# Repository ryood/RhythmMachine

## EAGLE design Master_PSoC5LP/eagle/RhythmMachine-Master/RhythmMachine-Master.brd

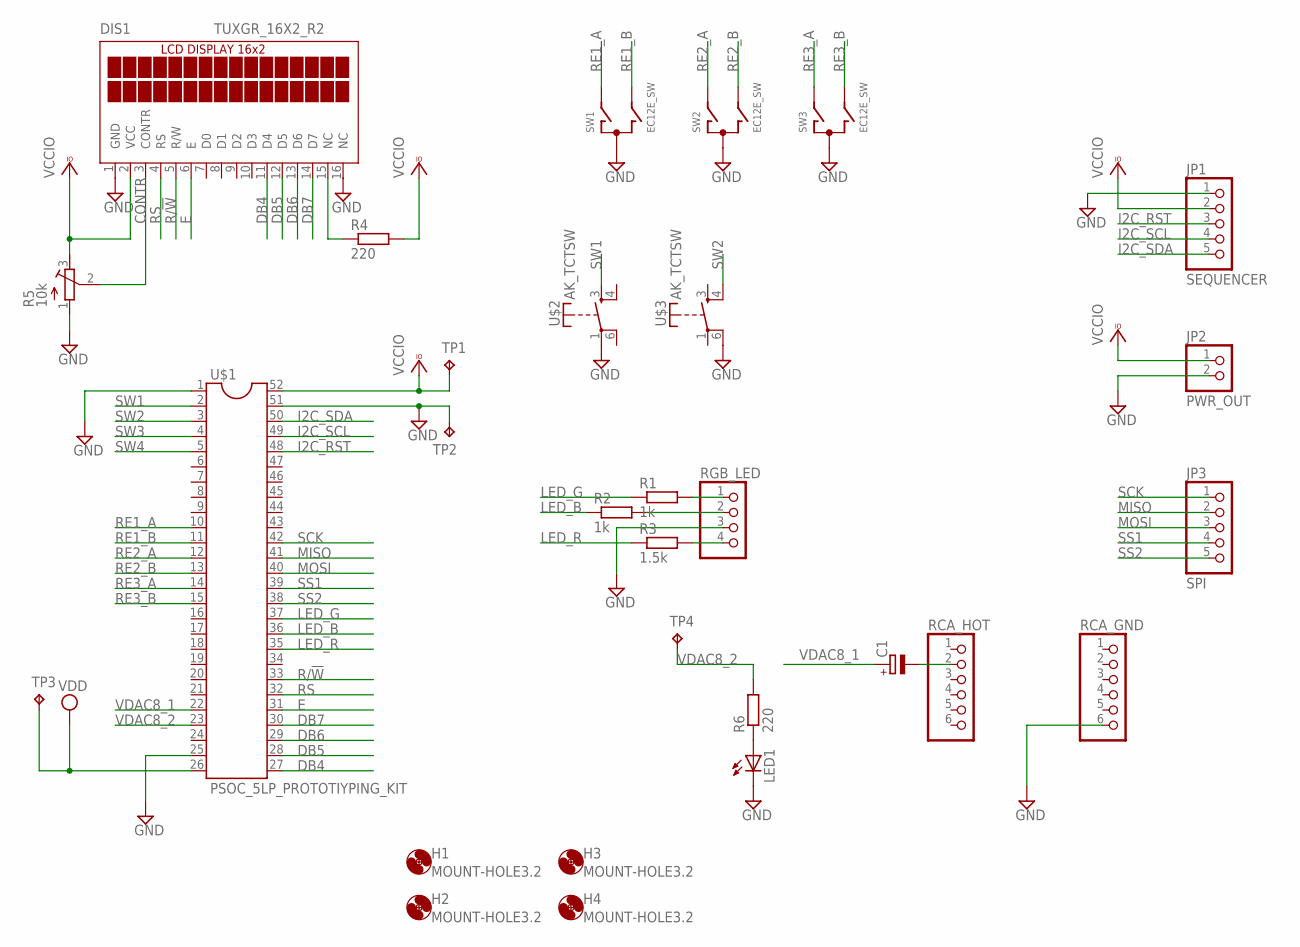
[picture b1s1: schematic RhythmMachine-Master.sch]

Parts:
C1: CPOL-EUE2.5-7; E2,5-7
DIS1: TUXGR_16X2_R2
H1, H2, H3, H4: MOUNT-HOLE3.2; 3,2
JP1: SEQUENCER; 1X05/90
JP2: PWR_OUT; 1X02/90
JP3: SPI; 1X05/90
LED1: LED3MM
R1, R2: 1k; 0207/7
R3: 1.5k; 0207/7
R4, R6: 220; 0207/7
R5: 10k; RTRIM3339P
RCA_GND: PINHD-1X6; 1X06
RCA_HOT: PINHD-1X6; 1X06
RGB_LED: PINHD-1X4; 1X04
SW1, SW2, SW3: EC12E_SW; ALPS_EC12E_SW
TP1, TP2, TP3, TP4: TPPAD1-13; P1-13
U$1: PSOC_5LP_PROTOTIYPING_KIT; DIL52-8
U$2, U$3: AK_TCTSW; TME1

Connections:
CONTR: DIS1.3 (CONTR), R5.2 (S)
DB4: DIS1.11 (D4), U$1.27
DB5: DIS1.12 (D5), U$1.28
DB6: DIS1.13 (D6), U$1.29
DB7: DIS1.14 (D7), U$1.30
E: DIS1.6 (E), U$1.31
GND: DIS1.1 (GND), DIS1.16 (NC), JP1.1, JP2.2, LED1.K (C), R5.1 (A), RCA_GND.6, RGB_LED.3, SW1.C, SW2.C, SW3.C, TP2.TP, U$1.1, U$1.25, U$1.51, U$2.1, U$3.6
I2C_RST: JP1.3, U$1.48
I2C_SCL: JP1.4, U$1.49
I2C_SDA: JP1.5, U$1.50
LED_B: R2.1, U$1.36
LED_G: R1.1, U$1.37
LED_R: R3.1, U$1.35
MISO: JP3.2, U$1.41
MOSI: JP3.3, U$1.40
unnamed: R1.2, RGB_LED.1
unnamed: R2.2, RGB_LED.2
unnamed: R3.2, RGB_LED.4
unnamed: DIS1.15 (NC), R4.1
unnamed: LED1.A, R6.1
unnamed: C1.-, RCA_HOT.2
R/!W: DIS1.5 (R/W), U$1.33
RE1_A: SW1.A, U$1.10
RE1_B: SW1.B, U$1.11
RE2_A: SW2.A, U$1.12
RE2_B: SW2.B, U$1.13
RE3_A: SW3.A, U$1.14
RE3_B: SW3.B, U$1.15
RS: DIS1.4 (RS), U$1.32
SCK: JP3.1, U$1.42
SS1: JP3.4, U$1.39
SS2: JP3.5, U$1.38
SW1: U$1.2, U$2.3 (S)
SW2: U$1.3, U$3.4 (S)
SW3: U$1.4
SW4: U$1.5
VCCIO: DIS1.2 (VCC), JP1.2, JP2.1, R4.2, R5.3 (E), TP1.TP, U$1.52
VDAC8_1: C1.+, U$1.22
VDAC8_2: R6.2, TP4.TP, U$1.23
VDD: TP3.TP, U$1.26

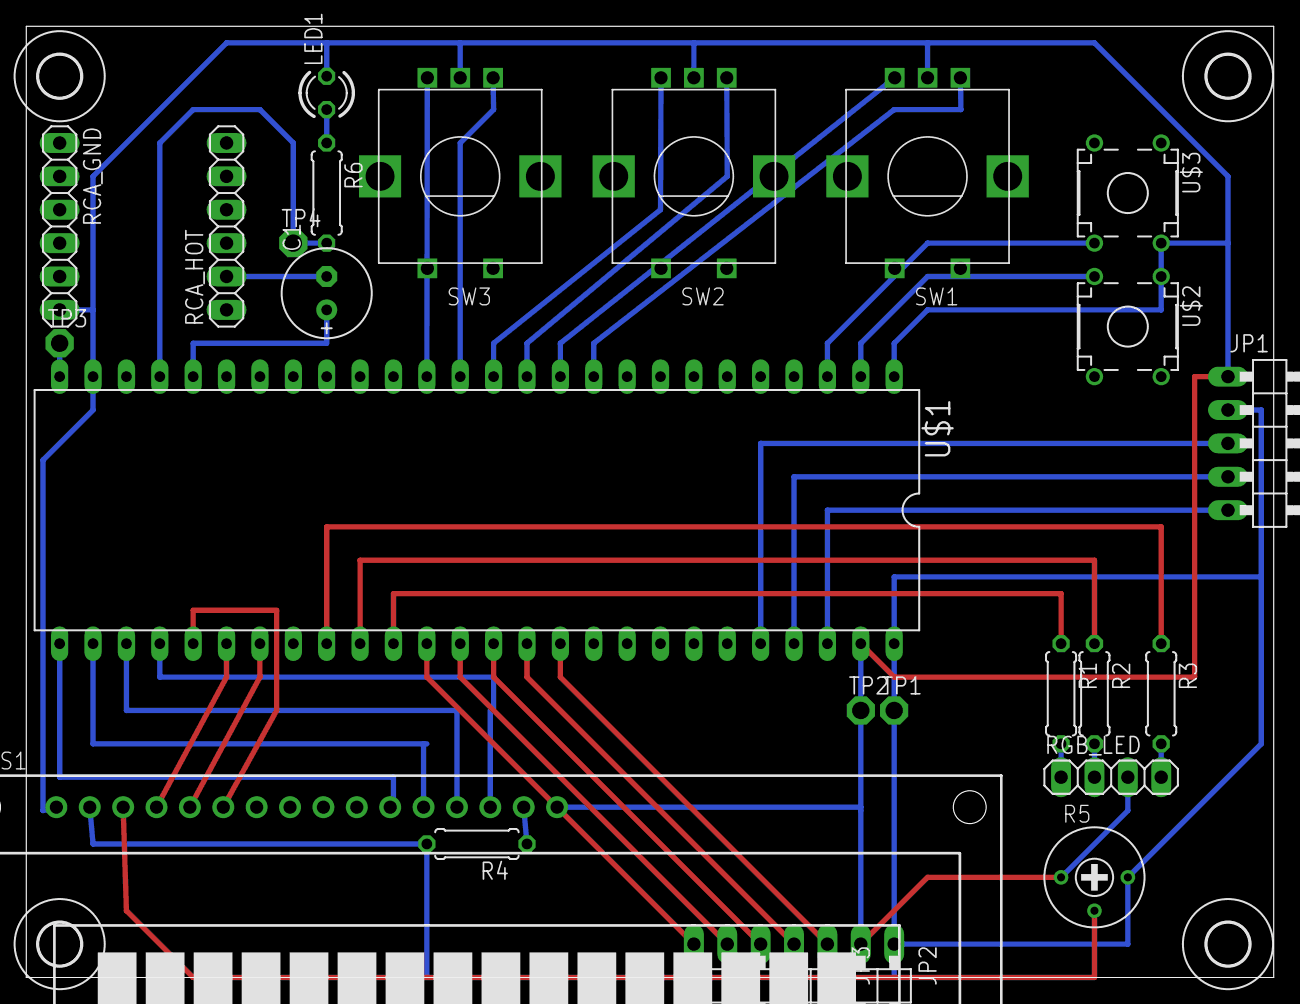
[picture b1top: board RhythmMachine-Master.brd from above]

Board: 2 copper layers, 94.9 x 72.4 mm, 29 parts (0 on the bottom side), 38 nets.

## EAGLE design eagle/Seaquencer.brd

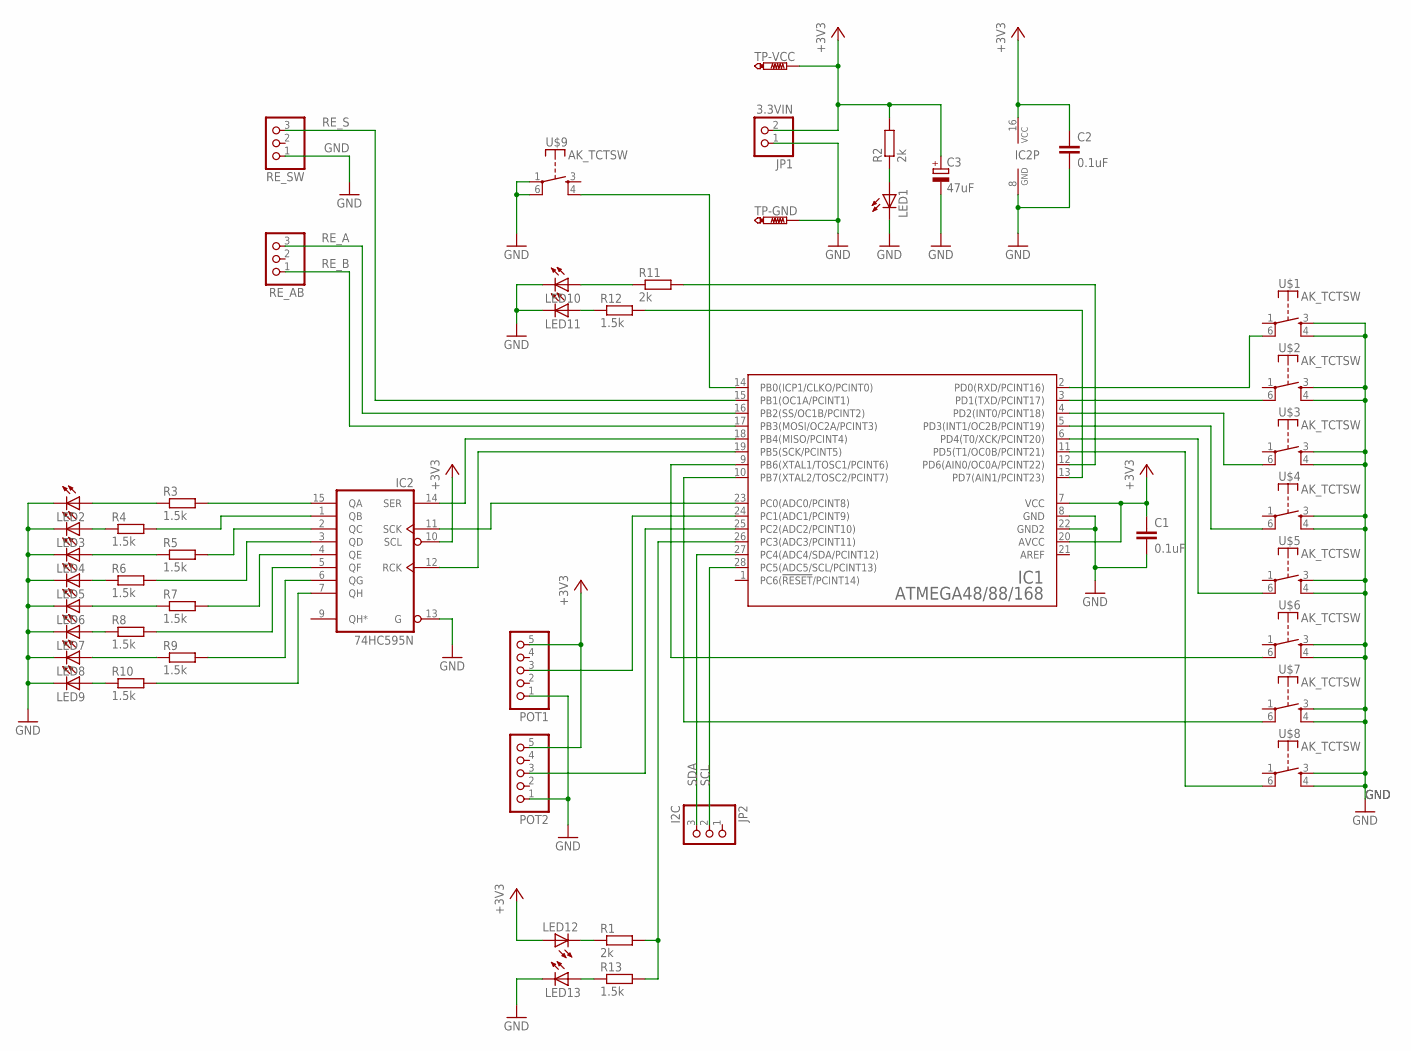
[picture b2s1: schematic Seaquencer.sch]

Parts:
C1, C2: 0.1uF; C025-024X044
C3: 47uF; E2,5-6
IC1: ATMEGA48/88/168; DIL28-3
IC2: 74HC595N; DIL16
JP1: 3.3VIN; 1X02
JP2: I2C; 1X03
LED1, LED2, LED3, LED4, LED5, LED6, LED7, LED8, LED9, LED10, LED11, LED12, LED13: LED3MM
POT1, POT2: PINHD-1X5; 1X05
R1, R2, R11: 2k; 0207/7
R3, R4, R5, R6, R7, R8, R9, R10, R12, R13: 1.5k; 0207/7
RE_AB: PINHD-1X3; 1X03
RE_SW: PINHD-1X3; 1X03
TP-GND: PTR1PAD1-13; P1-13
TP-VCC: PTR1PAD1-13; P1-13
U$1, U$2, U$3, U$4, U$5, U$6, U$7, U$8, U$9: AK_TCTSW; TME1

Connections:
+3V3: C1.1, C2.1, C3.+, IC1.7 (VCC), IC1.20 (AVCC), IC2.10 (SCL), IC2.16 (VCC), JP1.2, LED12.A, POT1.5, POT2.5, R2.2, TP-VCC.TP
GND: C1.2, C2.2, C3.-, IC1.8 (GND), IC1.22 (GND2), IC2.8 (GND), IC2.13 (G), JP1.1, LED1.K (C), LED2.K (C), LED3.K (C), LED4.K (C), LED5.K (C), LED6.K (C), LED7.K (C), LED8.K (C), LED9.K (C), LED10.K (C), LED11.K (C), LED13.K (C), POT1.1, POT2.1, RE_SW.1, TP-GND.TP, U$1.3 (S), U$1.4 (S), U$2.3 (S), U$2.4 (S), U$3.3 (S), U$3.4 (S), U$4.3 (S), U$4.4 (S), U$5.3 (S), U$5.4 (S), U$6.3 (S), U$6.4 (S), U$7.3 (S), U$7.4 (S), U$8.3 (S), U$8.4 (S), U$9.1, U$9.6
unnamed: IC1.2 (PD0(RXD/PCINT16)), U$1.6
unnamed: IC1.3 (PD1(TXD/PCINT17)), U$2.6
unnamed: IC1.11 (PD5(T1/OC0B/PCINT21)), U$8.6
unnamed: IC1.10 (PB7(XTAL2/TOSC2/PCINT7)), U$7.6
unnamed: IC1.9 (PB6(XTAL1/TOSC1/PCINT6)), U$6.6
unnamed: IC1.6 (PD4(T0/XCK/PCINT20)), U$5.6
unnamed: IC1.5 (PD3(INT1/OC2B/PCINT19)), U$4.6
unnamed: IC1.18 (PB4(MISO/PCINT4)), IC2.14 (SER)
unnamed: IC1.23 (PC0(ADC0/PCINT8)), IC2.11 (SCK)
unnamed: IC1.24 (PC1(ADC1/PCINT9)), POT1.3
unnamed: IC1.25 (PC2(ADC2/PCINT10)), POT2.3
unnamed: IC1.19 (PB5(SCK/PCINT5)), IC2.12 (RCK)
unnamed: IC1.14 (PB0(ICP1/CLKO/PCINT0)), U$9.4 (S)
unnamed: IC1.26 (PC3(ADC3/PCINT11)), R1.2, R13.2
unnamed: LED1.A, R2.1
unnamed: IC2.15 (QA), R3.2
unnamed: IC2.1 (QB), R4.2
unnamed: IC2.2 (QC), R5.2
unnamed: IC2.3 (QD), R6.2
unnamed: IC2.4 (QE), R7.2
unnamed: IC2.5 (QF), R8.2
unnamed: IC2.6 (QG), R9.2
unnamed: IC2.7 (QH), R10.2
unnamed: LED2.A, R3.1
unnamed: LED3.A, R4.1
unnamed: LED4.A, R5.1
unnamed: LED5.A, R6.1
unnamed: LED6.A, R7.1
unnamed: LED7.A, R8.1
unnamed: LED8.A, R9.1
unnamed: LED9.A, R10.1
unnamed: LED12.K (C), R1.1
unnamed: LED11.A, R12.1
unnamed: LED10.A, R11.1
unnamed: IC1.13 (PD7(AIN1/PCINT23)), R12.2
unnamed: IC1.12 (PD6(AIN0/OC0A/PCINT22)), R11.2
unnamed: LED13.A, R13.1
unnamed: IC1.4 (PD2(INT0/PCINT18)), U$3.6
RE_A: IC1.16 (PB2(SS/OC1B/PCINT2)), RE_AB.3
RE_B: IC1.17 (PB3(MOSI/OC2A/PCINT3)), RE_AB.1
RE_S: IC1.15 (PB1(OC1A/PCINT1)), RE_SW.3
SCL: IC1.28 (PC5(ADC5/SCL/PCINT13)), JP2.2
SDA: IC1.27 (PC4(ADC4/SDA/PCINT12)), JP2.3

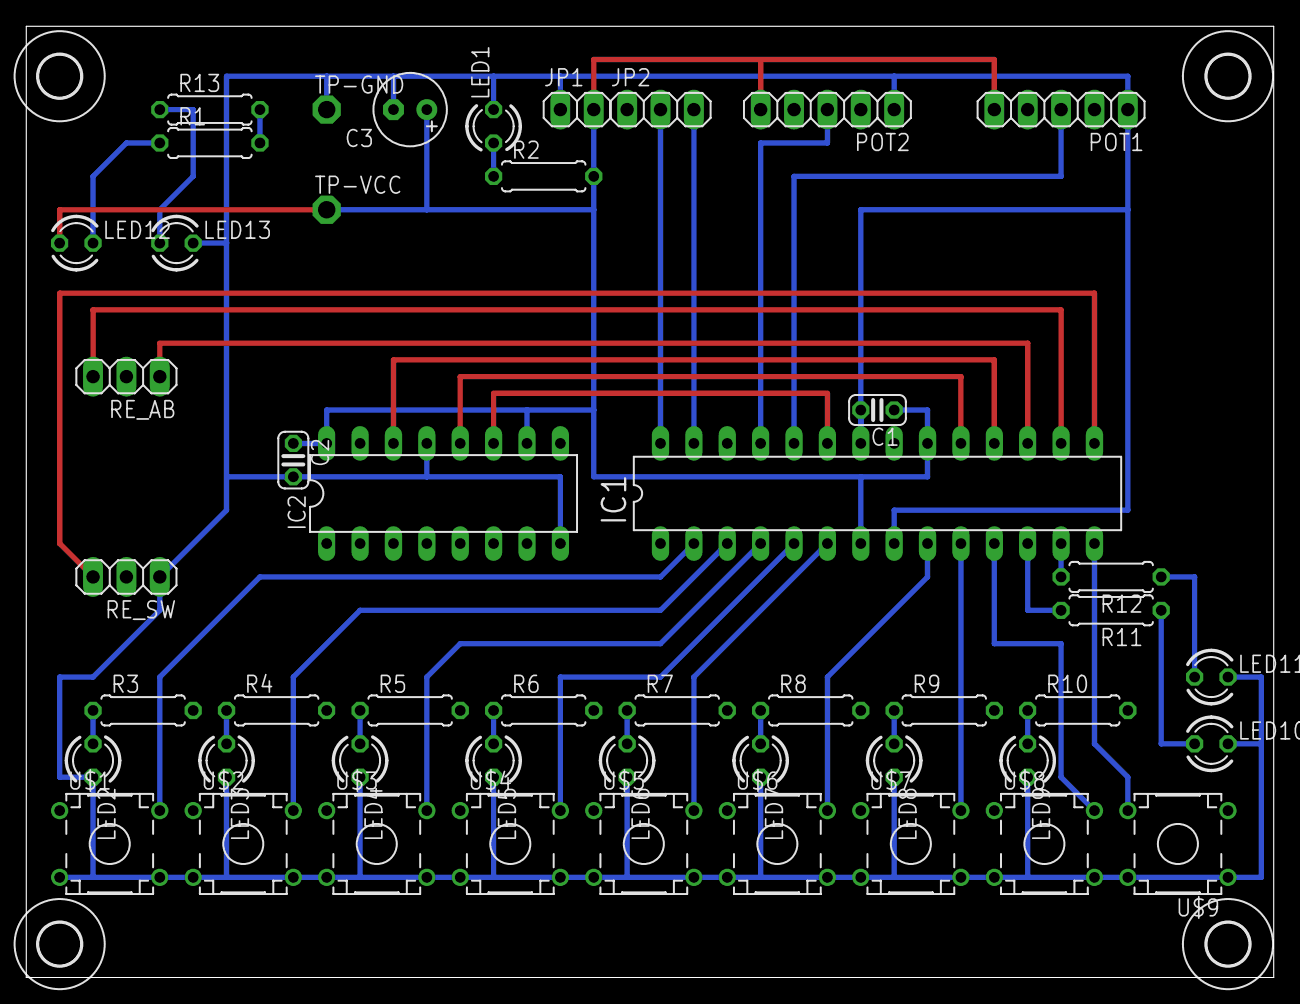
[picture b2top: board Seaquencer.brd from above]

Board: 2 copper layers, 94.9 x 72.4 mm, 52 parts (0 on the bottom side), 45 nets.

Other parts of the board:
U$10, U$11, U$12, U$13: 3,2

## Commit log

2015-08-24 Sequencer: POT追加前（完成形）
2015-08-24 Sequencer: POTを追加
2015-08-24 Sequencer: Add Jumper
2015-08-26 Add: Arduino Sketch, Atmel Studio Project (I2C Comm Test only).
2015-08-26 update: gitignore
2015-08-26 Sequencer_I2C_Slave.c: change to toggle mode
2015-08-26 Sequencer_I2C_Slave.c: add 74HC595 routine before main() implement
2015-08-26 Sequencer_I2C_Slave: implement 74HC595
2015-08-30 Add: Fritzing File
2015-08-30 Add Images
2015-08-30 ADD IC接続表
2015-08-30 Sequencer_I2C_Slave.c: I2Cを割り込み処理に変更
2015-08-30 Arduino: Sequencer_I2C_Master.ino: シリアル通信開始時にメッセージを表示
2015-08-30 Sequencer_I2C_Slave.c: ピン・チェンジ・インターラプトとチャタリング対策の実装 ->スイッチの同時押しは動作が変
2015-08-30 Sequencer_I2C_Slave.c: I2C Slave Addressを#defineに
2015-09-01 Sequencer_I2C_Slave.c: シーケンスをbyte配列に変更
2015-09-01 Sequencer_I2C_Slave.c, Sequencer_02.fzz: デバッグ用にPC3にLEDを追加
2015-09-01 Sequencer_I2C_Slave.c: TWIエラー時にステータスコードをLEDに表示
2015-09-01 Sequencer_I2C_Slave.c: シーケンスを2バイト送信
2015-09-01 Sequencer.brd: Add LED for Rotary Encdoer
2015-09-08 Add: Fritzing File: Sequencer_03.fzz
2015-09-08 Sequencer_I2C_Slave.c: Rotary Encoderのスイッチの処理を追加
2015-09-08 Sequencer_I2C_Slave.c: Rotary EncoderのABの処理を追加
2015-09-08 Sequencer_I2C_Slave.c: 若干修正
2015-09-08 Sequencer_I2C_Slave.c: POTのADCの処理を追加
2015-09-08 Sequencer_I2C_Slave.c: TWIのデータ送信順を変更
2015-09-08 Sequencer.brd: 部品再配置前
2015-09-11 回路図、基板図： Valueを設定
2015-09-11 画像を追加
2015-09-14 Add: Seqencer_I2C_データ・フォーマット.xlsx
2015-09-14 Sequencer.brd: Rotary Encoderの位置を移動
2015-09-14 抵抗値変更
2015-09-17 Sequencer.brd: Rotary Encoder付近のLEDの位置を変更
2015-09-21 Add: Sequencer_Test.xslx
2015-09-28 Sequencer_I2C_Slave.c, Sequencer_I2C_Master.ino: 再生中のNoteをLED表示
2015-09-28 Add: Rythm_Machine_全体案_ブレッドボード.png
2015-10-15 Add: Fritzing Files
2015-10-15 Add: PSoC_Fixedpoint_DDS_RhythmMachine Project
2015-10-16 PSoC_Fixedpoint_DDS_RhythmMachine: Optimized
2015-10-16 PSoC_Fixedpoint_DDS_RhythmMachine: Optimized (Compled Reslase mode)
2015-10-16 Add: PSoC_Fixedpoint_DDS_RhythmMachine 速度比較.xlsx
2015-10-21 ADD: PSoC_Fixedpoint_DDS_ThythmMachine_MCP4922 Project MCP4922で音出し→処理が追いつかない
2015-10-22 Add: PSoC_Fixedpoint_DDS_RhythmMachine_IDAC Project 内蔵IDACを使うプロジェクト
2015-10-22 MCP4922で実行時間を計測
2015-10-22 Sampling Clock: 16kHzに変更
2015-10-24 Add: Rythm_Machine_全体案_ver.2.fzz
2015-10-25 PSoC 4 Pioneer Kit & Sequencer Board & AQM1602.fzzの配線を修正
2015-10-25 Add: PSoC 4 Pioneer Kit & Sequencer Board & AQM1602_ブレッドボード.png
2015-10-25 new branch
2015-10-25 Update: PSoC 4 Pioneer Kit & Sequencer Board & AQM1602 & MCP4922.fzz
2015-10-25 Sequencer_Master_AQM1602_MCP4922: UARTを除去
2015-10-25 PSoC 4 Pioneer Kit & Sequencer Board & AQM1602 & MCP4922.fzz: SSの配線を修正
2015-10-25 Sequencer_Master_AQM1602_MCP4922: DACの動作を確認
2015-10-25 Sequencer_Master_AQM1602_MCP4922: SPI Clockを12MHzに変更
2015-10-25 Add: Sequencer_Master_AQM1602_MCP4922_DDS
2015-10-25 シーケンサー基板とI2C LCDをつなげて、リズムマシンの波形を出力 ※シーケンスの入力はまだ
2015-10-25 IC2バスを2系統に分割
2015-10-25 シーケンサー基板のLED表示と再生タイミングのリンクOK
2015-10-27 シーケンサー＆AQM１602&MCP4922のブレッドボード図を追加
2015-10-27 シーケンサーからの入力を反映(kickのみ)
2015-10-27 Rhythm_Machine_I2C_データ・フォーマット.xlsx変更
2015-10-27 Sequencer_I2C_Slave.c: 送信データの変更
2015-10-27 Sequencer_I2C_Slave.c: ADCの読み取り値を平均化
2015-10-27 Sequencer_I2C_Slave.c: ADCの読み取り値を平均化(DirtyフラグのタイミングをI2C通信時に変更)
2015-10-29 Sequencer_I2C_Slave: ソースコードを整理
2015-10-29 Sequencer_I2C_Slave: トラックの管理
2015-10-29 Sequencer_Master: 2015.10.29 シーケンサー基板からのデータを反映（2015.10.27版データフォーマット)
2015-10-29 Sequencer_I2C_Slave: I2C送信前にパラメータをストア
2015-10-29 Sequencer_Master_AQM1602_MCP4922_DDS_2_I2C: LCD表示のタイミングを調整
2015-10-29 Sequencer_Master_AQM1602_MCP4922_DDS_2_I2C: sequencerRdBufferを構造体に変更
2015-10-29 Sequencer_I2C_Slave: ADCを7bit Resolutionに
2015-10-29 Sequencer_Master_AQM1602_MCP4922_DDS_2_I2C: BPM変更の反映(ムリ？)
2015-10-31 Sequencer_I2C_Slave.c: POT1/POT2を4bit精度に→2つのPOTでBPMを設定
2015-10-31 Sequencer_Master: BPM変更の反映
2015-11-03 Sequencer_Master_AQM1602_MCP4922_DDS_2_I2C: SPLC792対応、REx2読み取り
2015-11-03 Sequencer_Master_AQM1602_MCP4922_DDS_2_I2C: LCD表示を修正
2015-11-03 Sequencer_Master_AQM1602_MCP4922_DDS_2_I2C: LCD制御関数をモジュール分割
2015-11-03 Sequencer_Master_AQM1602_MCP4922_DDS_2_I2C: ソースコードを整理
2015-11-03 2015.11.03 モジュレーション波形のDDSパラメータの計算の仕方を分離（ノイズあり）
2015-11-05 Sequencer_Master_AQM1602_or_SPLC792__MCP4922_DDS_2_I2C.cydsnに名前変更 ロータリーエンコーダimpl.
2015-11-05 Decay, Level impl.
2015-11-05 Decay, Level, Tone impl.
2015-11-07 Master_PSoC5LP_Testを追加
2015-11-08 Master_PSoC5LP_Test: 一時ファイルを削除
2015-11-08 PSoC 5LP Prototyping Kitでシーケンサー基板をテストするプロジェクトを追加
2015-11-09 Master_PSoC5LP_Test/Sequencer_Master_CQ_PSoC5LPプロジェクトを追加 UARTではなくCharacter LCDで表示
2015-11-12 Add: Master_PSoC5LP_Test
2015-11-12 Add: Sequencer_Master_CQ_PSoC5LP_HD44780 LCDにHD44780を使うように変更（作業前）
2015-11-12 Sequencer_Master_CQ_PSoC5LP_HD44780: LCDにHD44780を使うように変更
2015-11-12 Sequencer_Master_CQ_PSoC5LP_HD44780: impl. Sampling Timer
2015-11-13 Add: Sequencer_Master_PSoC5LP_ProtoKit_HD44780.cydsn PSoC 5LP Prototyping Kitに移植
2015-11-13 Sequencer_Master_PSoC5LP_ProtoKit_HD44780.cydsn Master Clockを72MHzに変更
2015-11-13 Sequencer_Master_PSoC5LP_ProtoKit_HD44780 ロータリーエンコーダをインプリメント
2015-11-14 Sequencer_Master_PSoC5LP_ProtoKit_HD44780 波形生成をモジュール分割
2015-11-15 Sequencer_Master_PSoC5LP_ProtoKit_HD44780 VDAC8からの出力をインプリメント
2015-11-15 PSoC 5LP Prototyping Kit & Sequencer Board & HD44780 REx3.fzz DAC出力にLEDインジケータを追加
2015-11-15 Sequencer_Master_PSoC5LP_ProtoKit_HD44780 波形生成をインプリメント
2015-11-15 Rhythm_Machine_I2C_データ・フォーマット.xlsx トラック数を8に変更
2015-11-15 Sequencer_I2C_Slave トラック数を8に変更 トラック切り替えのロータリーエンコーダのデバウンスを調整
2015-11-15 Sequencer_Master_PSoC5LP_ProtoKit_HD44780 波形をLED表示用に出力
2015-11-15 Sequencer_Master_PSoC5LP_ProtoKit_HD44780 LCDに再生中のノートを流れる様に表示 '^'
2015-11-17 Sequencer_Master_PSoC5LP_ProtoKit_HD44780.cydsn play/stopをインプリメント
2015-11-17 Sequencer_Master_PSoC5LP_ProtoKit_HD44780.cydsn Levelの重み付けを修正
2015-11-18 Sequencer_Master_PSoC5LP_ProtoKit_HD44780.cydsn ピンアサインを実装に向けて変更
2015-11-18 Sequencer_Master_PSoC5LP_ProtoKit_HD44780.cydsn Tact Switchの読み取りを追加
2015-11-19 Master_PSoC5LP: Eagleファイルを追加
2015-11-19 Add: Rhythm Machine Main Board PSoC 5LP Prototyping Kit Pin Assign.xlsx
2015-11-19 Master_PSoC5LP: Eagleファイル: 基板図を作成
2015-11-19 Rhythm Machine Main Board PSoC 5LP Prototyping Kit Pin Assign ピンアサインを変更
2015-11-19 Add: Rhythm Machine Master PSoC 5LP Prototyping Kit.fzz
2015-11-20 Sequencer_Master_PSoC5LP_ProtoKit_HD44780.cydsn デジタルフィルタの処理を追加
2015-11-21 add: DDS_Test.cydsn filterd noiseテスト中
2015-11-21 Add: DDS_Test_UART.cydsn
2015-11-21 Add: DDS_Test_VDAC.cydsn
2015-11-21 DDS_Test_VDAC.cydsn Timer割り込みではなくループでテスト
2015-11-22 一旦FIX Sequencer_Master_PSoC5LP_ProtoKit_HD44780.cydsn
2015-11-22 Eagle: 修正
2015-11-22 Sequencer_Master_PSoC5LP_ProtoKit_HD44780.cydsn LEDのピンアサインを変更
2015-11-22 masterにリベース
2015-11-22 Rhythm Machine Main Board PSoC 5LP Prototyping Kit Pin Assign.xlsxを更新
2015-11-23 Sequencer_Master_PSoC5LP_ProtoKit_HD44780.cydsn シーケンス表示をカスタムフォントに変更
2015-11-23 Sequencer_I2C_Slave チャタリング防止間隔を128usに変更
2015-11-23 Sequencer_IC接続表 更新
2015-11-26 Eagleファイル修正
2015-11-26 マスター基板テスト表追加 RhythmMachine_Master_Board_テスト表20151125.xlsx
2015-11-26 Sequencer_Master.cywrk I2CのSCL, SDAを内部プルアップするように変更
2015-11-27 ファイルを整理
2015-11-27 Sequencer Master ノイズ生成テスト開始
2015-11-28 Sequencer Master: 8bitでノイズ生成テスト
2015-11-28 Sequencer Master: Filtered Noiseを実装
2015-11-28 Sequencer Master: Hihatのパラメータを調整
2015-11-28 RhythmMachine: モジュレーション波形を調整
